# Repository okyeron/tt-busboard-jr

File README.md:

# TT-Busboard-Jr.

A small powered i2c busboard for the monome/teletype i2c ecosystem

This is compact powered i2c busboard suitable for use with Monome Teletype, Trilogy and other i2c modules. 

Provides three i2c / ii headers with pull-ups to support larger i2c / ii networks.

You can connect up to six modules with regular (1x3) i2c jumpers, or more using "flying bus" cables to connect multiple modules in series.

This busboard is designed to just hang out in the back of your rack - rather than be directly attached to a module.

PCBs and full-built versions of this project are available via https://denki-oto.weebly.com
Or just make you own!

## bom

* (3) header, male, 2x3 
* (1) 3v3 voltage regulator AZ1117CH-3.3TRG1DICT-ND
* (2) resistor 0805 2.2k 
* (1) header, male, shrouded, 2x5 

Adapted from the [Teletype Busboard](https://github.com/monome/tt-busboard) by Brian Crabtree (Monome)

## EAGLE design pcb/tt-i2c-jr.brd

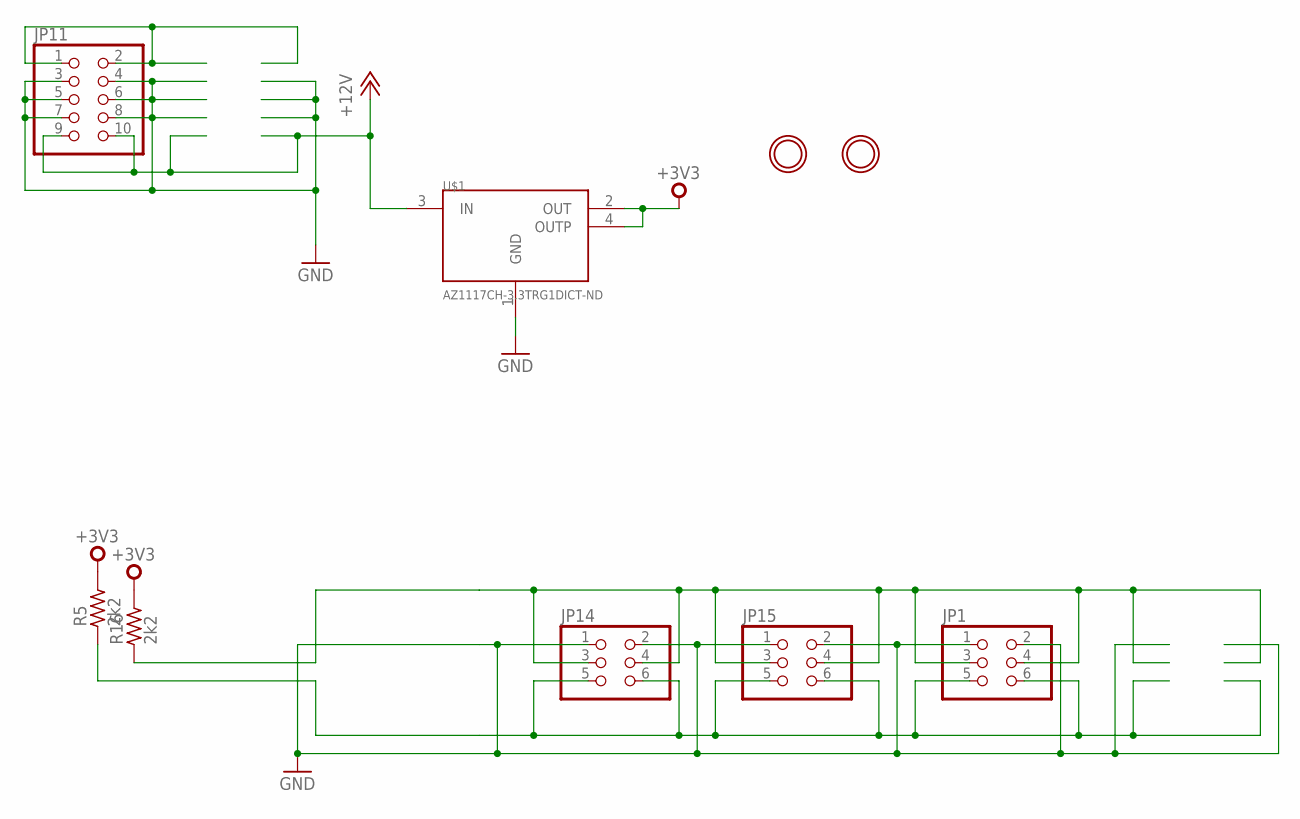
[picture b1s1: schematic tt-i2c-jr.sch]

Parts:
JP1, JP14, JP15: PINHD-2X3; 2X03
JP11: PINHD-2X5; 2X05
R5, R16: 2k2; R1206
U$1: AZ1117CH-3.3TRG1DICT-ND; SOT223
U$2, U$3: MOUNTINGHOLE3.0THIN; MOUNTINGHOLE_3.0_PLATEDTHIN

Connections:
+3V3: R5.2, R16.2, U$1.2 (OUT), U$1.4 (OUTP)
+12V: JP11.9, JP11.10, U$1.3 (IN)
GND: JP1.1, JP1.2, JP11.3, JP11.4, JP11.5, JP11.6, JP11.7, JP11.8, JP14.1, JP14.2, JP15.1, JP15.2, U$1.1 (GND)
unnamed: JP11.1, JP11.2
SCL: JP1.3, JP1.4, JP14.3, JP14.4, JP15.3, JP15.4, R16.1
SDA: JP1.5, JP1.6, JP14.5, JP14.6, JP15.5, JP15.6, R5.1

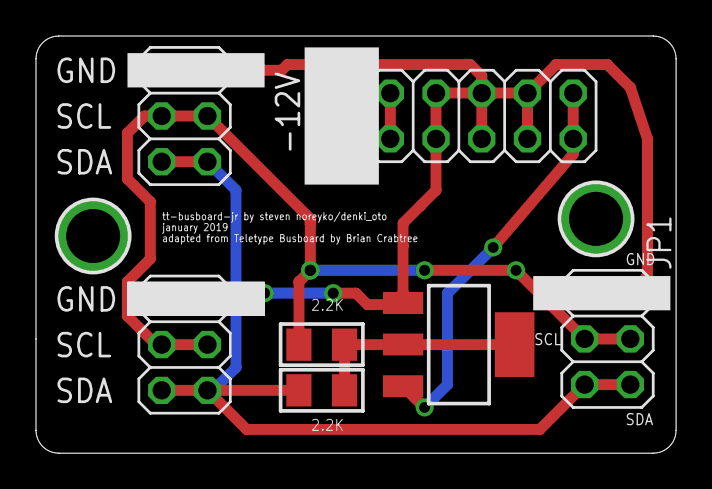
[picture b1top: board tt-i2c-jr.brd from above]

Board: 2 copper layers, 35.6 x 23.2 mm, 9 parts (0 on the bottom side), 6 nets.

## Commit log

2019-01-13 add readme
2019-01-13 add folders
2019-01-13 pictures
2019-01-13 typos
2019-01-13 attribution
2019-01-13 add dxf for back cover
2019-01-15 updated board files/dxf
2019-01-16 gerber tweaks

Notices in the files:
parts and their libraries:
microbuilder: This work is placed in the public domain, and may be freely used for commercial and non-commercial work with the following conditions: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
